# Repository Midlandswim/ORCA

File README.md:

# O.R.C.A
Optimized Rocketry Computer Assembly

This is in partnership with Dhalwani Designs, which holds all rights, data, and procedures for this project and the related. <br />

Researcher: Wilson Dhalwani <br />
Aides: Mr. Michael Liva (BCA) & Mr. Joseph Barbetta (BCA) & Mr. Vladyslav Kharechko (BCA) <br />
Context: Dhalwani Designs Sanctioned Project, Senior Capstone, and Electrical Engineering Research Project <br />
Project Name: The Optimized Rocketry Computer Assembly <br />
Start Date: June 06, 2023 <br /> 

The following repository is for documenting and sharing my work in this research and capstone project and its related fields of electrical and avionics engineering. This was also made to record my process of solving the issue at hand so that others can learn and build upon my work. The O.R.C.A was inspired by work and research with various competitive rocketry teams, who came with concerns for traditional flight computers, which tended to be large, involved, and bulky, affecting performance and technical usage. This led to me going down a rabbit hole of avionics and the niche community that came with flight computer design. After spending hours in KiCAD, EAGLE, and JLCPCB Assembly Libraries, I found myself intrigued by the idea of an ultra-compact, one that was far smaller than the conventional flight computer and many times more capable. And, after many weeks of research and design, I came up with the first prototype for O.R.C.A, a board that was 60 mm by 72 mm, however, this was not good enough. Small was the name of the game, and with the discovery of 0402 SMD components, I managed to bring it down to less than 47 mm by 34 mm, small enough to fight in the palm of your hand! I would eventually bring this work over, as part of my Senior Engineering Capstone (yes, I am ahead of schedule), to hopefully share my work in avionics so that others could be inspired by what I did, and collaborate towards even smaller boards. The evolution of Printed Circuit Board design is at its peak, and the innovation in the electronics industry is mesmerizing, allowing for some cool creations and hopefully even more compact and powerful designs in the future. With that being said, optimized is used loosely, as I am sure in a month or so, we will have components even smaller than 0201 generally available, especially with the recent advances in Flex PCBs. I completely designed the entire system, top-down, using KiCAD, snapEDA for parts libraries, and JLCPCB for SMD component libraries. The amazing thing about this board, despite its size and power, is its capability and the ability to be applied to many scenarios and uses. With the great populace of onboard sensors, abundant and expandable memory, and the amazing MCU, this board can be programmed for rockets, drones, and more. Currently, time is being spent on updating and improving firmware, and work is currently being done on a new and improved version 4.0, so be on the lookout for that in the coming months! This project has no end date as an innovation never ends, rather, continues until the idea is forgotten, and my hope is that this work can be the basis for future engineers who, too, find great excitement in innovation and design. <br />

Should you have any questions, comments, or just wish to reach out, email me at wilson.dhalwani@gmail.com !

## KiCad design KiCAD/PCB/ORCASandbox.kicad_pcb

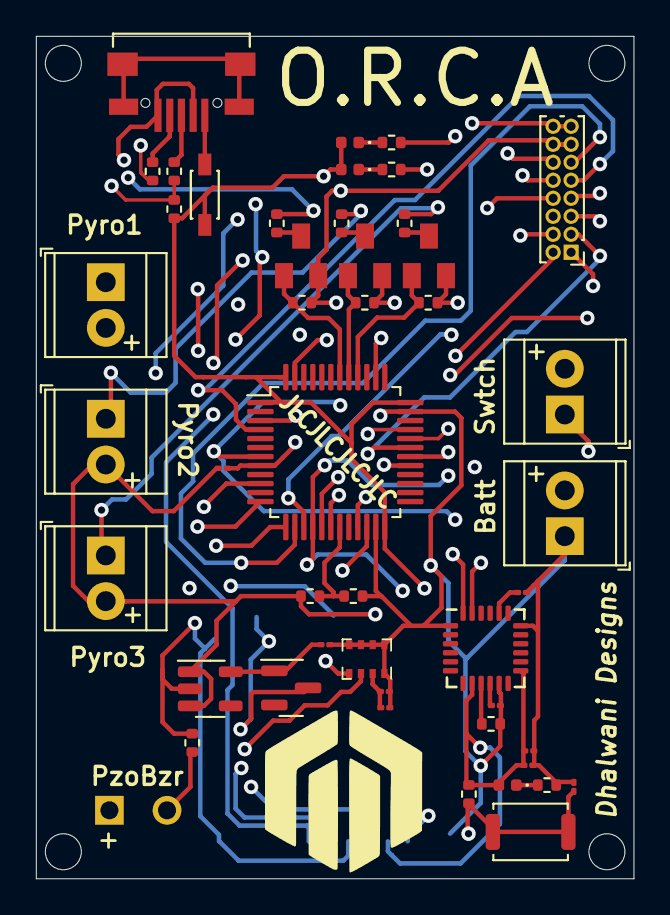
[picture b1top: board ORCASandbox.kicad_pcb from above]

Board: 4 copper layers, 33.2 x 46.8 mm, 48 parts (1 on the bottom side), 45 nets.

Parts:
BZR1: PiezoBuzzer; MagneticBuzzer_Kingstate_KCG0601
Battery1: Screw_Terminal_01x02; TerminalBlock_TE_282834-2_1x02_P2.54mm_Horizontal
BluLED1: LED2; LED_0402_1005Metric
CAP1, CAP9: 47uF; C_01005_0402Metric
CAP2, CAP4, CAP5: 0.1uF; C_01005_0402Metric
CAP3: 2.2e-2uF; C_01005_0402Metric
CAP6, CAP7: 10uF; C_01005_0402Metric
CRNT-LMT-RS1, CRNT-LMT-RS2, CRNT-LMT-RS3: 1Ω; R_0402_1005Metric
D1: B140HW-7; SOD3715X135N
D2: BAT54C; SOT-23
GrnLED1: LED1; LED_0402_1005Metric
J1: Pins_02x08_P1.27mm_TH; PinHeader_2x08_P1.00mm_Vertical
LEDRES1: 51Ω; R_0402_1005Metric
LEDRES2, LEDRES3: 27Ω; R_0402_1005Metric
MCRO1: Micro_SD_Card; MOLEX_503398-1892
MICROCNTRL1: STM32F103C8T6; LQFP-48_7x7mm_P0.5mm
PULL-DWN-RS1, PULL-DWN-RS2, PULL-DWN-RS3: 470Ω; R_0402_1005Metric
PZORES1: 1Ω; R_0402_1005Metric
Pyro1, Pyro2, Pyro3: Screw_Terminal_01x02; TerminalBlock_TE_282834-2_1x02_P2.54mm_Horizontal
Q1, Q2, Q3: AO3400A; SOT23
R1: 10kΩ; R_0402_1005Metric
R2, R3: 22Ω; R_0402_1005Metric
R4: 1.5kΩ; R_0402_1005Metric
R5: 4.2Ω; R_0402_1005Metric
R6: 3Ω; R_0402_1005Metric
RES1: 4.7kΩ; R_0402_1005Metric
RSTCAP1: 0.1uF; C_01005_0402Metric
RSTSWTCH1: SW_MEC_5G; SW_Push_SPST_NO_Alps_SKRK
RedLED1: LED3; LED_0402_1005Metric
Switch1: Screw_Terminal_01x02; TerminalBlock_TE_282834-2_1x02_P2.54mm_Horizontal
U1: BMP280; Bosch_LGA-8_2x2.5mm_P0.65mm_ClockwisePinNumbering
U2: MPU-6050; InvenSense_QFN-24_4x4mm_P0.5mm
U3: XC6210B332MR; SOT-23-5
USB1: MICROQTJ; SHOUHAN_MICROQTJ

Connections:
3.3V: BluLED1.2 (A), CAP1.2, CAP9.2, D1.A, D2.3, GrnLED1.2 (A), J1.15, J1.16, MCRO1.6 (VSS), MCRO1.9 (VSS), MICROCNTRL1.1 (VBAT), MICROCNTRL1.24 (VDD), MICROCNTRL1.36 (VDD), MICROCNTRL1.48 (VDD), R1.1, R4.2, RedLED1.2 (A), U2.8 (VLOGIC), U2.13 (VDD)
3.3VOut: CAP7.1, D2.1, U3.5 (VOUT)
BATT+: Battery1.2, Switch1.2
BUZZ: BZR1.1 (-), MICROCNTRL1.29 (PA8)
CS_SD_Card: MCRO1.2 (CD/DAT3^2), MICROCNTRL1.38 (PA15)
GND: Battery1.1, CAP1.1, CAP2.2, CAP3.2, CAP4.2, CAP5.2, CAP6.2, CAP7.2, CAP9.1, J1.13, J1.14, LEDRES1.2, MCRO1.4 (VDD), MCRO1.P1 (SHIELD), MCRO1.P2 (SHIELD), MCRO1.P3 (SHIELD), MCRO1.P4 (SHIELD), MICROCNTRL1.8 (VSSA), MICROCNTRL1.23 (VSS), MICROCNTRL1.35 (VSS), MICROCNTRL1.47 (VSS), PULL-DWN-RS1.2, PULL-DWN-RS2.2, PULL-DWN-RS3.2, PZORES1.2, Q1.2 (S), Q2.2 (S), Q3.2 (S), R6.2, RES1.2, RSTCAP1.2, U1.1 (GND), U1.5 (SDO), U1.6 (VDDIO), U1.7 (GND), U1.8 (VDD), U2.1 (CLKIN), U2.11 (FSYNC), U2.18 (GND), U3.2 (GND), USB1.2 (D-), USB1.5 (GND)
GPIO1: J1.12, MICROCNTRL1.13 (PA3)
GPIO2: J1.11, MICROCNTRL1.14 (PA4)
GPIO3: J1.10, MICROCNTRL1.3 (PC14)
GPIO4: J1.9, MICROCNTRL1.4 (PC15)
LED_BLU: LEDRES2.2, MICROCNTRL1.12 (PA2)
LED_RED: LEDRES3.2, MICROCNTRL1.10 (PA0)
MISO: J1.5, MCRO1.7 (DAT0), MICROCNTRL1.16 (PA6)
MOSI: J1.7, MCRO1.3 (CMD), MICROCNTRL1.17 (PA7)
NRST: J1.8, MICROCNTRL1.7 (NRST), R1.2, RSTCAP1.1, RSTSWTCH1.1 (A), RSTSWTCH1.2 (A)
unnamed: BZR1.2 (+), PZORES1.1
unnamed: BluLED1.1 (K), LEDRES2.1
unnamed: D1.PWR, USB1.1 (PWR)
unnamed: GrnLED1.1 (K), LEDRES1.1
unnamed: CRNT-LMT-RS1.2, Pyro1.1
unnamed: CRNT-LMT-RS2.2, Pyro2.1
unnamed: CRNT-LMT-RS3.2, Pyro3.1
unnamed: CRNT-LMT-RS1.1, Q1.3 (D)
unnamed: CRNT-LMT-RS2.1, Q2.3 (D)
unnamed: CRNT-LMT-RS3.1, Q3.3 (D)
unnamed: LEDRES3.1, RedLED1.1 (K)
unnamed: CAP4.1, CAP5.1, U1.2 (CSB)
unnamed: RES1.1, U2.9 (AD0)
unnamed: CAP3.1, U2.20 (CPOUT)
unnamed: CAP2.1, U2.10 (REGOUT)
unnamed: R3.1, USB1.3 (D+)
unnamed: R2.1, USB1.4 (ID)
PY1: MICROCNTRL1.42 (PB6), PULL-DWN-RS1.1, Q1.1 (G)
PY2: MICROCNTRL1.41 (PB5), PULL-DWN-RS2.1, Q2.1 (G)
PY3: MICROCNTRL1.40 (PB4), PULL-DWN-RS3.1, Q3.1 (G)
SCK: J1.6, MCRO1.5 (CLK), MICROCNTRL1.15 (PA5)
SCL: J1.4, MICROCNTRL1.21 (PB10), U1.4 (SCK), U2.23 (SCL)
SDA: J1.2, MICROCNTRL1.22 (PB11), U1.3 (SDI), U2.24 (SDA)
SD_CD: MCRO1.10 (DETECT_SWITCH), MICROCNTRL1.18 (PB0)
UART_RX: J1.3, MICROCNTRL1.31 (PA10)
UART_TX: J1.1, MICROCNTRL1.30 (PA9)
USB_D+: MICROCNTRL1.33 (PA12), R3.2, R4.1
USB_D-: MICROCNTRL1.32 (PA11), R2.2
VBAT: MICROCNTRL1.19 (PB1), R5.2, R6.1
VCC: CAP6.1, Pyro1.2, Pyro2.2, Pyro3.2, R5.1, Switch1.1, U3.1 (VIN), U3.3 (CE)

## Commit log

2023-06-04 Create Code
2023-06-04 Create Schematics
